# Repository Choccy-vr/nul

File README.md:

# nul
A WLED controller that blends into the background

## Description
Nul is a small, compact WLED controller that is meant to go in line with your LED strip. Powered by an ESP32 C3 in a super small 11x40mm package.

## Instructions 
1. Plug the board into your computer and update WLED if you need to (preinstalled with v16.0.1)
2. Connect your LED Strip to your board
3. Attach your antenna
4. Plug in any USB PD Power source and enjoy
5. Connect to the WLED-AP Access point and connect it to the internet.

## BOM
|Product Name|Product Description|Product Link       |Product Cost|Total |
|------------|-------------------|-------------------|------------|------|
|PCB         |PCB + PCBA         |https://jlcpcb.com/|$47.22      |$54.60|

## Pictures

### Schematic

### PCB

### Built

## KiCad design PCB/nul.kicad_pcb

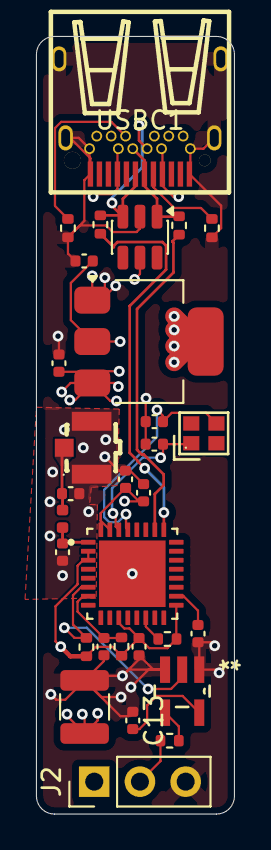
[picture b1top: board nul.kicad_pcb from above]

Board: 4 copper layers, 11.0 x 43.2 mm, 30 parts (0 on the bottom side), 19 nets.

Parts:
C2, C3, C4, C5, C13: 0.1uF ceramic; C_0402_1005Metric
C6: 1uF; C_0402_1005Metric
C7, C8: 15pF; C_0402_1005Metric
C9, C10: 1.5pF; C_0402_1005Metric
C11, C12: 10uf; C_0402_1005Metric
C14: 220uf; C_1210_3225Metric
J2: LED Socket; PinHeader_1x03_P2.54mm_Vertical
JP2: U.FL-R-SMT-1; RF-SMD_FRF05002-JSS103M
L1: L; L_0402_1005Metric
R1, R2, R3: 10k; R_0402_1005Metric
R4, R8, R9: 33Ohm; R_0402_1005Metric
R5, R6: 5.1k; R_0402_1005Metric
U1: ESP32-C3FH4; QFN50P500X500X90-33N
U2: AMS1117-3.3; SOT-223-3_TabPin2
U3: SN74AHCT1G125DBVR; DBV5
U4: XRCGB40M000F1S1DR0; CRYSTAL-SMD_4P-L2.0-W1.6-BL
U5: SRV05-4; SOT-23-6
USBC1: FUC-24F11-SNLB1; USB-C-SMD_C67380

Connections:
+3.3V: C2.2, C4.2, C5.2, C12.1, R1.1, R2.1, R3.1, U1.2 (VDD3P3), U1.3 (VDD3P3), U1.11 (VDD3P3_RTC), U1.17 (VDD3P3_CPU), U1.31 (VDDA), U1.32 (VDDA), U2.2 (VO)
+5V: C11.1, C13.2, C14.1, J2.1, U2.3 (VI), U3.5 (VCC), U5.5 (VP), USBC1.A4 (VBUS), USBC1.A9 (VBUS), USBC1.B4 (VBUS), USBC1.B9 (VBUS)
/USB_DATA+: R8.1, U1.25 (GPIO18/USB_D-)
/USB_DATA-: R9.1, U1.26 (GPIO19/USB_D+)
GND: C2.1, C3.2, C4.1, C5.1, C6.1, C7.2, C8.1, C9.2, C10.2, C11.2, C12.2, C13.1, C14.2, J2.3, JP2.2 (GND), JP2.3 (GND), R5.1, R6.1, U1.33 (GND), U2.1 (GND), U3.1 (*OE), U3.3 (GND), U5.2 (VN), USBC1.13 (EP), USBC1.14 (EP), USBC1.15 (EP), USBC1.16 (EP), USBC1.A1 (GND), USBC1.A12 (GND), USBC1.B1 (GND), USBC1.B12 (GND)
LED: R2.2, U1.6 (GPIO2), U3.2 (A)
unnamed: J2.2, R4.2
unnamed: C10.1, JP2.1 (SIG), L1.1
unnamed: C6.2, R1.2, U1.7 (CHIP_EN)
unnamed: R3.2, U1.14 (GPIO8)
unnamed: C9.1, L1.2, U1.1 (LNA_IN)
unnamed: C3.1, U1.18 (VDD_SPI)
unnamed: C7.1, U1.29 (XTAL_N), U4.3
unnamed: C8.2, U1.30 (XTAL_P), U4.1
unnamed: R4.1, U3.4 (Y)
unnamed: R5.2, USBC1.A5 (CC1)
unnamed: R6.2, USBC1.B5 (CC2)
USB_D+: R9.2, U5.1 (IO1), USBC1.A6 (DP1), USBC1.B6 (DP2)
USB_D-: R8.2, U5.3 (IO2), USBC1.A7 (DN1), USBC1.B7 (DN2)

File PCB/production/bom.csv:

Designator,Footprint,Quantity,Value,LCSC Part #
"C10, C9",0402,2,1.5pF,C1552
"C11, C12",0402,2,10uf,
"C13, C2, C3, C4, C5",0402,5,0.1uF ceramic,C1525
C14,1210,1,220uf,C400951
C6,0402,1,1uF,C52923
"C7, C8",0402,2,15pF,C1548
J2,PinHeader_1x03_P2.54mm_Vertical,1,LED Socket,
JP2,RF-SMD_FRF05002-JSS103M,1,U.FL-R-SMT-1,C88374
L1,0402,1,L,C27122
"R1, R2, R3",0402,3,10k,C25744
"R4, R8, R9",0402,3,33Ohm,C25105
"R5, R6",0402,2,5.1k,C25905
U1,QFN50P500X500X90-33N,1,ESP32-C3FH4,
U2,SOT-223-3_TabPin2,1,AMS1117-3.3,C6186
U3,DBV5,1,SN74AHCT1G125DBVR,
U4,CRYSTAL-SMD_4P-L2.0-W1.6-BL,1,XRCGB40M000F1S1DR0,C1870453
U5,SOT-23-6,1,SRV05-4,C7420376
USBC1,USB-C-SMD_C67380,1,FUC-24F11-SNLB1,C67380
